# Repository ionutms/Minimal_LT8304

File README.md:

# Minimal_LT8304

## Overview

This repository contains a minimal KiCad design project for the Analog Devices LT8304, a monolithic micropower isolated flyback converter. The project includes schematic designs and PCB layout files for implementing this versatile isolated power supply IC.

## Disclaimer

> [!NOTE]
> This project is provided "as is" and without any warranty, express or implied. For more details, please see the [LICENSE](LICENSE) file.

## About the LT8304

The LT8304 from Analog Devices is a monolithic micropower isolated flyback converter. It samples the isolated output voltage directly from the primary-side flyback waveform, eliminating the need for a third winding or an opto-isolator for regulation.

Key features include:

- **Input Voltage Range:** 3V to 100V.
- **Power Switch:** An internal 2A, 150V DMOS power switch is integrated.
- **Quiescent Current:** It has a low quiescent current of 116μA in sleep mode and 390μA in active mode.
- **Operation Modes:** It utilizes quasi-resonant boundary mode operation at heavy loads and low ripple Burst Mode® operation at light loads.
- **Package:** It is available in a thermally enhanced 8-lead SO package.
- **Power Delivery:** Can deliver up to 24W of isolated output power.
- **Output Voltage Setting:** The output voltage is set using two external resistors, with an option for a third resistor for temperature compensation.
- **Communication:** Uses a Serial Peripheral Interface (SPI) for configuration and data transfer.
- **Operating Temperature Range:** -40°C to +125°C.

## Project Structure

```
minimal_lt8304/
├── minimal_lt8304.kicad_sch       # Main schematic file
├── minimal_lt8304.kicad_pcb       # PCB layout file
├── minimal_lt8304.kicad_pro       # Project configuration file
├── fp-lib-table                     # Footprint library table
├── sym-lib-table                    # Symbol library table
├── project_jobs_set.kicad_jobset    # Project job settings
├── ibom.config.ini                  # Interactive BOM configuration
├── docs/                            # Documentation files
│   ├── pictures/                    # Images and photos
│   ├── schematics/                  # Schematic PDF exports
│   └── 3d_models/                   # 3D model files
└── KiCAD_Symbols_Generator/         # Submodule for symbol generation from CSV data
```

## Project Features

This design provides a minimal implementation of the LT8304 with the following features:

- **Power Supply:**
  - Wide input voltage range from 3V to 100V.
- **Channel Configuration:**
  - Isolated flyback converter configuration.
- **Bill of Materials (BOM):**
  - Interactive HTML BOM (`ibom.html`) for easy component identification and sourcing.
- **Libraries:**
  - Comprehensive symbol and footprint libraries integrated as a submodule.
- **3D Model:**
  - Includes a 3D model of the board for better visualization.

## Getting Started

### Prerequisites

- [KiCad EDA](https://www.kicad.org/) version 9.0 or later installed on your system
- Git (for cloning the repository and submodule management)

### Opening the Project

1. **Clone the repository** (including submodules):
   ```bash
   git clone --recursive https://github.com/ionutms/Minimal_LT8304.git
   ```
   
   If you've already cloned the repository without submodules, initialize them with:
   ```bash
   git submodule init
   git submodule update
   ```

2. **Open the project in KiCad**:
   - Launch KiCad
   - Click "Open Existing Project"
   - Navigate to the cloned repository folder
   - Select the `minimal_lt8304.kicad_pro` file

3. **Explore the design**:
   - Open the schematic editor to view the circuit design
   - Open the PCB editor to view the board layout
   - Review the symbol and footprint libraries used in the design

### Project Files

- **Main schematic**: `minimal_lt8304.kicad_sch` - Contains the primary circuit design with the LT8304 and support components
- **PCB layout**: `minimal_lt8304.kicad_pcb` - Physical board design file with proper component placement
- **Project configuration**: `minimal_lt8304.kicad_pro` - KiCad project settings

## Dependencies

This project has the following dependencies:

### 1. KiCAD Symbols Generator

This repository uses [KiCAD_Symbols_Generator](https://github.com/ionutms/KiCAD_Symbols_Generator) as a submodule for custom symbol generation.

To initialize the submodule after cloning this repository:

```bash
git submodule update --init --recursive
```

### 2. 3D Models

This project requires the [3D_Models_Vault](https://github.com/ionutms/3D_Models_Vault) repository for 3D models.

#### Setup for KiCAD 9:

1. Clone the 3D models repository:
   ```bash
   git clone https://github.com/ionutms/3D_Models_Vault.git
   ```

2. In KiCAD 9, add an environment variable:
   - Variable name: `KICAD9_3D_MODELS_VAULT`
   - Variable value: Full path to where you cloned the 3D_Models_Vault repository

## Usage

After setting up the dependencies, open the project in KiCad 9 to access all features including the 3D models.

## Symbol Generator Submodule

This project includes the KiCAD_Symbols_Generator as a submodule, which provides tools for generating KiCad symbols from CSV data files. For more information on using this tool, see the [KiCAD_Symbols_Generator documentation](minimal_lt8304/KiCAD_Symbols_Generator/README.md).

## Documentation

The `docs` folder contains:
- Schematic PDF exports
- Images and photos of the design
- 3D model files (GLB and WRL formats)

## Visuals

The following images showcase the PCB design from different perspectives:

*Top View of the PCB*

*Side View of the PCB*

*Bottom View of the PCB*

## License

This project is licensed under the MIT License - see the [LICENSE](LICENSE) file for details.

## References

- [LT8304 Datasheet](https://www.analog.com/media/en/technical-documentation/data-sheets/lt8304-8304-1.pdf)
- [KiCad EDA](https://www.kicad.org/)

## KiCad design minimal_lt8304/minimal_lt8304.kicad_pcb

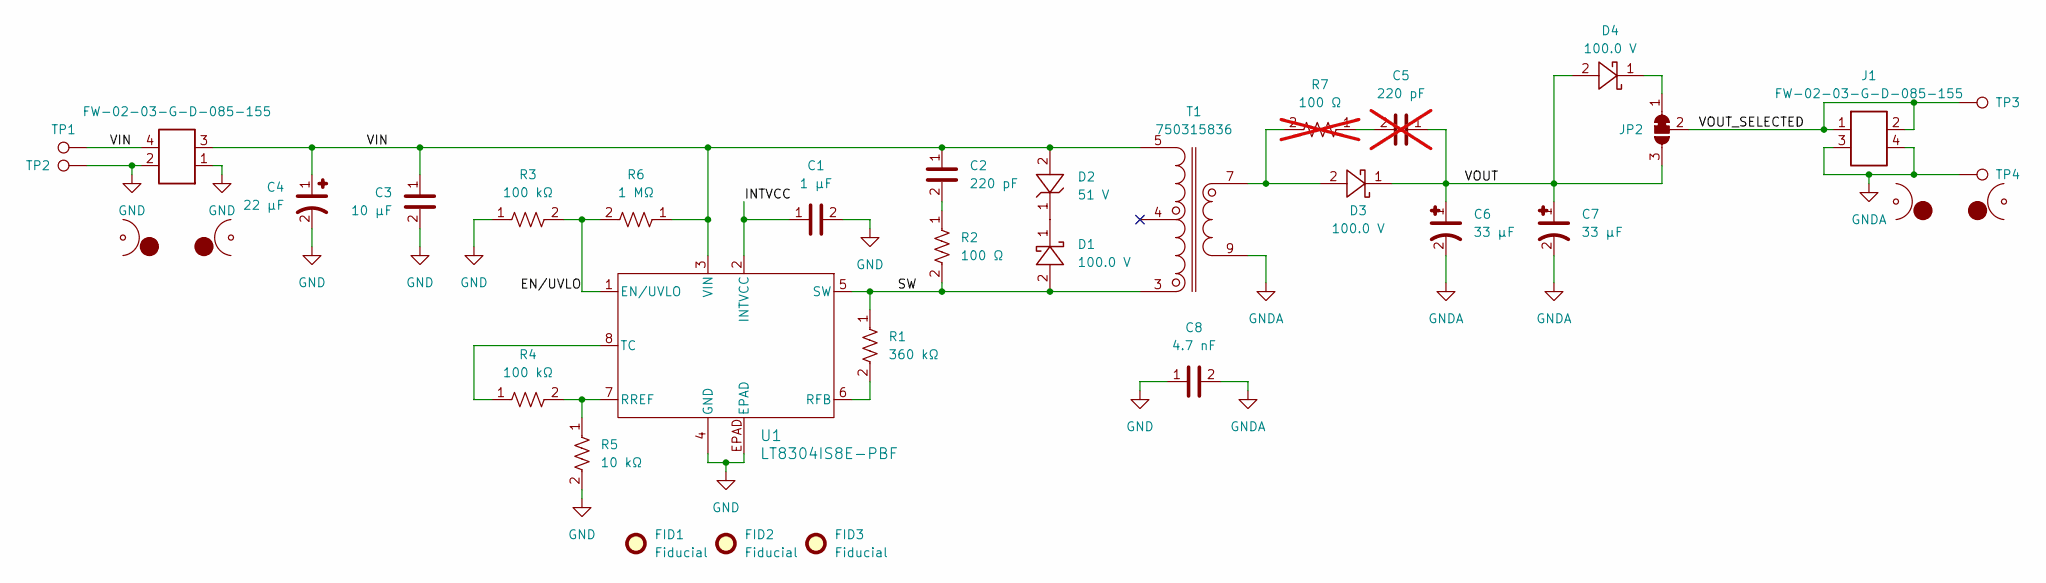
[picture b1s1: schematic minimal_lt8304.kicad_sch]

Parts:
C1: 1 µF; C_1206_3216Metric; Tolerance 10%; Voltage Rating 25V; MPN C1206R105K3RAC7800
C2: 220 pF; C_0603_1608Metric; Tolerance 5%; Voltage Rating 50V; MPN CC0603JRNPO9BN221
C3: 10 µF; C_1206_3216Metric; Tolerance 10%; Voltage Rating 50V; MPN CL31B106KBHNNN#
C4: 22 µF; C_023x0248_5_9x6_3Metric; Tolerance 20%; Voltage Rating 50V; MPN 50SVPK22M22
C5: 220 pF; C_0603_1608Metric; Tolerance 5%; Voltage Rating 50V; MPN CC0603JRNPO9BN221; not fitted
C6, C7: 33 µF; C_034x0263_8_0x6_7Metric; Tolerance 20%; Voltage Rating 50V; MPN A768KE336M1HLAE042336
C8: 4.7 nF; C_1210_140_3225Metric; Tolerance 10%; Voltage Rating 1.5kV; MPN C1210C472KFRACAUTO
D1, D3, D4: 100.0 V; SOD123W; MPN PMEG10020AELR
D2: 51 V; SOD323; MPN BZX384-B51
FID1, FID2, FID3: Fiducial; Fiducial_0.5mm_Mask1mm
J1, J2: FW-02-03-G-D-085-155; Current Rating (A) 5.2; Voltage Rating (V) 300; MPN FW-02-03-G-D-085-155
JP2: SolderJumper_3_Open; SolderJumper-3_P1.3mm_Bridged_1_2_RoundedPad1.0x1.5mm_Numbe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
MB1, MB2: mouse-bite-midle-50mil-200mil
R1: 360 kΩ; R_0805_2012Metric; Tolerance 1%; Voltage Rating 150V; MPN RC0805FR-07360KL
R2: 100 Ω; R_0603_1608Metric; Tolerance 1%; Voltage Rating 75V; MPN CRCW0603100RFKEAHP
R3, R4: 100 kΩ; R_0402_1005Metric; Tolerance 5%; Voltage Rating 50V; MPN ERJ-2GEJ104X
R5: 10 kΩ; R_0402_1005Metric; Tolerance 1%; Voltage Rating 50V; MPN ERJ-2RKF1002X
R6: 1 MΩ; R_0603_1608Metric; Tolerance 1%; Voltage Rating 75V; MPN ERJ-3EKF1004V
R7: 100 Ω; R_0603_1608Metric; Tolerance 1%; Voltage Rating 75V; MPN CRCW0603100RFKEAHP; not fitted
T1: 750315836; Tolerance ±10%; MPN 750315836
TP1, TP2, TP3, TP4: TestPoint; TestPoint_THTPad_Castelated
U1: LT8304IS8E-PBF; S_8E_ADI

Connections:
/EN/UVLO: R3.2, R6.2, U1.1 (EN/UVLO)
/INTVCC: C1.1, U1.2 (INTVCC)
/SW: D1.2, R1.1, R2.2, T1.3, U1.5 (SW)
/VIN: C2.1, C3.1, C4.1, D2.2, J2.3, J2.4, R6.1, T1.5, TP1.1, U1.3 (VIN)
/VOUT: C5.1, C6.1, C7.1, D3.1, D4.2, JP2.3 (B)
/VOUT_SELECTED: J1.1, J1.2, JP2.2 (C), TP3.1
GND: C1.2, C3.2, C4.2, C8.1, J2.1, J2.2, R3.1, R5.2, TP2.1, U1.4 (GND), U1.EPAD
GNDA: C6.2, C7.2, C8.2, J1.3, J1.4, T1.9, TP4.1
unnamed: C2.2, R2.1
unnamed: C5.2, R7.1
unnamed: D1.1, D2.1
unnamed: D3.2, R7.2, T1.7
unnamed: D4.1, JP2.1 (A)
unnamed: R1.2, U1.6 (RFB)
unnamed: R4.2, R5.1, U1.7 (RREF)
unnamed: R4.1, U1.8 (TC)

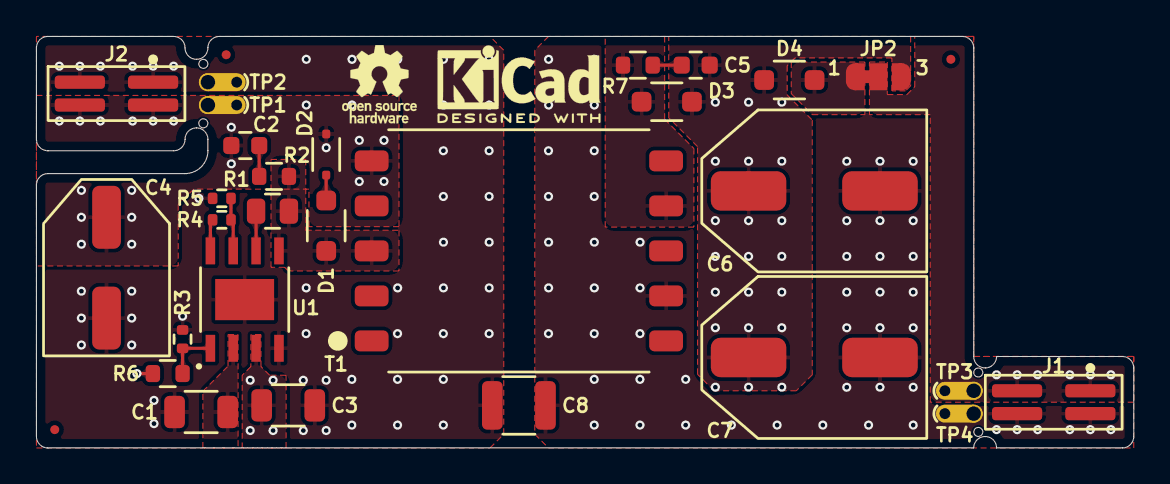
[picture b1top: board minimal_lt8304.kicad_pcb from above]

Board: 4 copper layers, 61.0 x 22.9 mm, 33 parts (0 on the bottom side), 16 nets.

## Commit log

2025-03-12 Add initial KiCad project files for minimal_lt8304
2025-03-12 Add submodule for KiCAD Symbol Generator
2025-03-12 Add footprint and symbol library tables for KiCad project
2025-03-12 Update KiCad project files and submodule reference for minimal_lt8304
2025-03-13 Update KiCad project configuration and add ibom configuration file
2025-03-14 Update project
2025-03-14 Update ibom configuration to include additional component blacklist
2025-03-16 Remove submodule reference for KiCAD Symbol Generator
2025-03-16 Add submodule reference for KiCAD Symbols Generator
2025-03-16 Update footprint library URIs to use KiCAD Symbols Generator
2025-03-18 Switch to KiCad 9
2025-03-19 Add .log files to .gitignore
2025-03-19 Add project job set configuration for minimal_lt8304
2025-03-19 Update minimal_lt8304 project files and add side image
2025-03-19 Refactor project job set configuration for minimal_lt8304 to streamline 3D export settings
2025-03-19 Update minimal_lt8304 binary files for improved 3D export and side image representation
2025-03-20 Add special_execute command for rendering top view of minimal_lt8304 PCB
2025-03-20 Update subproject reference for KiCAD Symbols Generator in minimal_lt8304
2025-03-20 Update minimal_lt8304 binary files and add top view image for enhanced visualization
2025-03-21 Update project job set configuration for minimal_lt8304 to enhance output paths and add front and right view rendering
2025-03-21 Remove obsolete top and side images for minimal_lt8304 and add new 3D model and additional view images
2025-03-21 Update README.md to include project dependencies and setup instructions for KiCAD and 3D models
2025-03-21 Small project update
2025-03-21 Update 3D model and add new front and right view images for minimal_lt8304
2025-04-02 Update 3D model and replace top, side, front, and right view images for minimal_lt8304
2025-04-18 Update default zoom factor in kicad-config.yml to improve visibility
2025-04-18 Update KiCad documentation (schematics and PCB renders)
2025-04-18 Update default zoom factor in kicad-config.yml to enhance visibility
2025-04-25 development backup
2025-04-25 Refactor KiCad configuration and update workflow to utilize new zoom factors and improve output handling
2025-04-25 Remove unused schematic and image files for minimal LT8304
2025-04-25 Update KiCad documentation for minimal_lt8304 (schematics and PCB renders)
2025-04-25 Adjust side view zoom factor and pan settings in KiCad configuration
2025-04-25 Adjust side view pan setting in KiCad configuration
2025-05-07 Update subproject commit for KiCAD Symbols Generator
2025-05-24 Add GitHub Actions workflow to generate KiCad 3D models
2025-05-25 Update trigger branch for KiCad 3D models generation workflow
2025-08-18 Update KiCAD configuration and workflow files
2025-08-22 Update GitHub workflow files for KiCad automation
2025-08-29 Update GitHub workflows for KiCad models and jobs
2025-09-02 Update README.md with comprehensive project documentation
2025-10-05 chore: update workflows from central repository
2025-10-05 chore: update workflows and kicad config from central repository
2025-10-26 Update kicad-config workflow settings
